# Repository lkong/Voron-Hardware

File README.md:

# Voron-Hardware
Cool Hardware designed by the Voron Design group

| Project   |      Overview      |  
|----------|---------------|
| Hall Effect Endstop | Replacement for mechanical endstop switches with an adjustable magnetic endstop PCB |
| Klipper Expander    | Standalone MCU for use with Klipper with various inputs and outputs                 |
| Nano Display        | Adapts an Arduino Nano to the RepRap standard 2 2x5pin IDC Connectors               |
| Taco Raven          | 3D Printer controller with 8 integrated stepper drivers for use with Klipper |
| Toolhead Board      | Remix of Klipper Expander to fit on a toolhead mounted to a nema17 or 40mm fan |

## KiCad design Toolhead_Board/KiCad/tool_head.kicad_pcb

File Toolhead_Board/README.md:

# STM32-Tool-Heade-Board

Simple MCU board for use with Klipper 3D Printer firmware with:
 - STM32F042F6P6 MCU with internal oscilator
 - 4 Mosfet outputs (1 3A one for hotend, 3 for fans)
 - 2 Thermistor inputs
 - 1 GPIO header

 Parts that need to be sourced if assembled by JLC:
  - Micro USB port [Molex 105017-0001](https://www.digikey.com/product-detail/en/molex/1050170001/WM1399CT-ND/2350885) or equivalent [Amazon](https://www.amazon.com/gp/product/B01IQ8VN94)
  - Resettable Fuse [MF-R800](https://www.digikey.com/en/products/detail/bourns-inc/MF-R800/259980)
  - 2 Pin Tactile Switch [6 x 3.5mm Button](https://www.digikey.com/product-detail/en/c-k/PTS636-SP43-LFS/CKN12304-ND/10071717) or [Amazon](https://www.amazon.com/flashtree-3x6x4-3H-Momentary-Tactile-Button/dp/B083R566PK/ref=sr_1_13)
  - Screw Terminals [5.08mm Screw Terminals](https://www.digikey.com/product-detail/en/on-shore-technology-inc/OSTTA024163/ED2580-ND/614529)

To flash:
  1 Bridge BOOT1 with solder
  2 Flash
  3 disconnect BOOT1

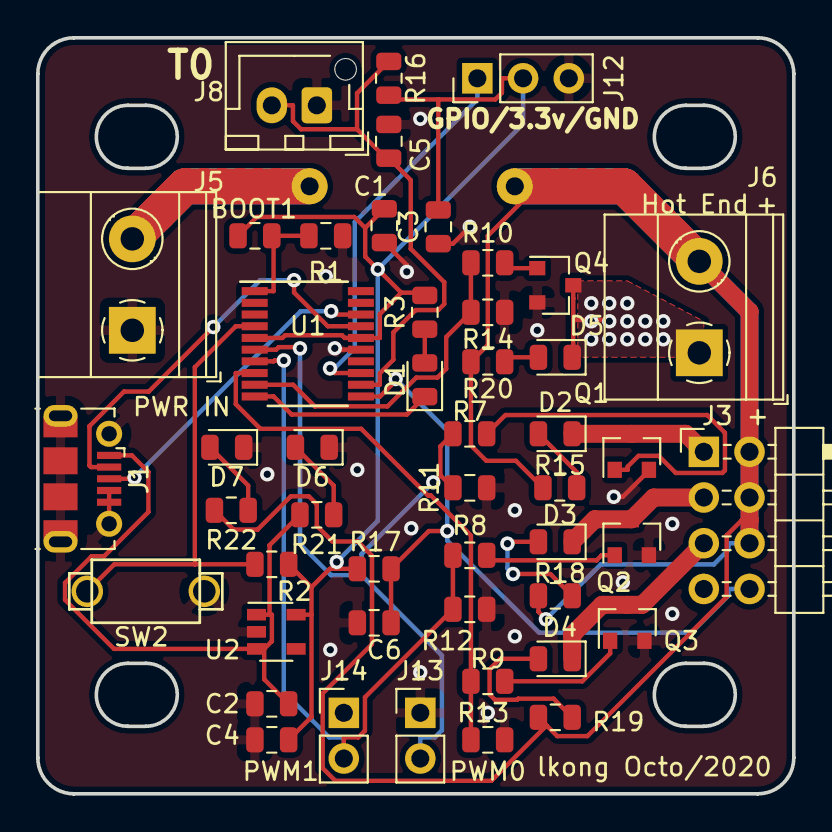
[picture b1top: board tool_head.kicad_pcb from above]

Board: 2 copper layers, 42.0 x 42.0 mm, 49 parts (1 on the bottom side), 32 nets.

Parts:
BOOT1: 0R; R_0805_2012Metric
C1, C3: 0.1uF; C_0805_2012Metric
C2, C4: 4.7uF; C_0805_2012Metric
C5, C6: 10uF; C_0805_2012Metric
D1, D2, D3, D4, D5, D6, D7: LED; LED_0805_2012Metric
F1: Fuse; Fuse_Littelfuse-LVR200
J1: USB_B_Micro; USB_Micro-B_Molex-105017-0001
J3: Conn_02x04_Odd_Even; PinHeader_2x04_P2.54mm_Horizontal
J5: Vin; 1x02_ScrewTerminal_Phoenix
J6: HotEnd; 1x02_ScrewTerminal_Phoenix
J8: Conn_01x02; JST_XH_B2B-XH-AM_1x02_P2.50mm_Vertical
J12: Conn_01x03; PinHeader_1x03_P2.54mm_Vertical
J13, J14: Conn_01x02; PinHeader_1x02_P2.54mm_Vertical
Q1, Q2, Q3, Q4: IRLML6344TRPBF; SOT-23
R1, R2, R11, R12, R13, R14: 10K; R_0805_2012Metric
R3, R21: 1K; R_0805_2012Metric
R7, R8, R9, R10: 100; R_0805_2012Metric
R15, R16, R17, R18, R19, R20, R22: 4.7K; R_0805_2012Metric
SW2: SW_SPST; 2PinTactileButton
U1: STM32F042F6Px; TSSOP-20_4.4x6.5mm_P0.65mm
U2: AP2127K-3.3; SOT-23-5

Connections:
+3V3: BOOT1.2, C1.2, C3.2, C4.2, J12.2, R2.1, R3.2, R16.2, R17.2, U1.5, U1.16, U2.5
/BOOT0: BOOT1.1, R1.2, U1.1
/D+: J1.3, U1.18
/D-: J1.2, U1.17
/LED: D1.1, U1.10
/Mosfet0: D2.1, J3.1, Q1.3
/Mosfet1: D3.1, J3.3, Q2.3
/Mosfet2: D4.1, J3.5, Q3.3
/Mosfet3: D5.1, J6.1, Q4.3
/VBUS: C2.2, J1.1, R21.2, U2.1, U2.3
/Vin: F1.1, J3.2, J3.4, J3.6, J6.2, R15.1, R18.1, R19.1, R20.1, R22.2
/~RESET: R2.2, SW2.2, U1.4
GND: C1.1, C2.1, C3.1, C4.1, C5.1, C6.1, D6.1, D7.1, J1.4, J1.5, J1.6, J3.7, J5.1, J8.1, J12.3, J13.1, J14.1, Q1.2, Q2.2, Q3.2, Q4.2, R1.1, R11.2, R12.2, R13.2, R14.2, SW2.1, U1.15, U2.2
GPIO: J12.1, U1.13
unnamed: D1.2, R3.1
unnamed: D2.2, R15.2
unnamed: D3.2, R18.2
unnamed: D4.2, R19.2
unnamed: D5.2, R20.2
unnamed: D6.2, R21.1
unnamed: D7.2, R22.1
unnamed: F1.2, J5.2
unnamed: Q1.1, R7.2
unnamed: Q2.1, R8.2
unnamed: Q3.1, R9.2
unnamed: Q4.1, R10.2
PWM0: J13.2, R7.1, R11.1, U1.6
PWM1: J14.2, R8.1, R12.1, U1.7
PWM2: R9.1, R13.1, U1.8
PWM3: R10.1, R14.1, U1.9
T0: C5.2, J8.2, R16.1, U1.12
T1: C6.2, J3.8, R17.1, U1.11

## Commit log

2020-10-13 revision v2, fixed boot pin bug
